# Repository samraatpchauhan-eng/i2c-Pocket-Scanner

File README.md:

# i2c Pocket Scanner
i2c Pocket scanner is a portable hardware debugging device, for scanning i2c modules' hexadecimal code and displaying it to the user. I designed it mainly for use if you use public makerspaces alot and don't have the space for a full hardware debugging kit, or need to verify if a part works on the go. 
## Features:
* **Miniature Layout:**  The i2c Pocket Scanner has a very small footprint, making it easy to carry it in your bag, or put it in your pocket!
* **OLED display:** There is a 0.91 inch oled screen to display the hexadecimal code received from the component being tested, and to verify the part actually works.
* **Simple Assembly:** Assembling the i2c Pocket Scanner is simple, and easy, as there is only the Seeed Xiao rp2040 and the OLED display to connect to the PCB.

---

## CAD Model
Due to the small size of the case, everything fits together nice and tight, without an risk of damage. There is also engravings on the case, describing what each header hole is so connecting external components becomes easy

### Case Assembly & Fitment
*A 3D CAD visualization highlighting how all the parts fit together seamlessly.*

---

## PCB Design
The underlying electronics were engineered in KiCad. The board features clean routing paths optimized for the RP2040 pin configurations and a direct connection layout to handle both the OLED display and the open header for connecting other components.

### Schematic Design
*The circuit schematic mapping the display routing, and header connections to the microcontroller.*

### PCB Layout Architecture
*The routed printed circuit board design detailing trace paths, footprints, and physical alignment.*

---

## How to Flash
1. Press and hold the physical **BOOT** button on the RP2040 controller board.
2. Connect the USB cable while holding the button, then release it.
3. A virtual drive named will mount to your operating system.
4. Drag and drop the `i2c-pocket-scanner.ino.uf2` binary file directly onto the root of the drive.
5. The device will automatically flash, reboot, and initialize as an operational device.

---

## AI Attribution Note
**Please Note that AI was utilized for some basic project planning and debugging of the firmware in VS.Code**

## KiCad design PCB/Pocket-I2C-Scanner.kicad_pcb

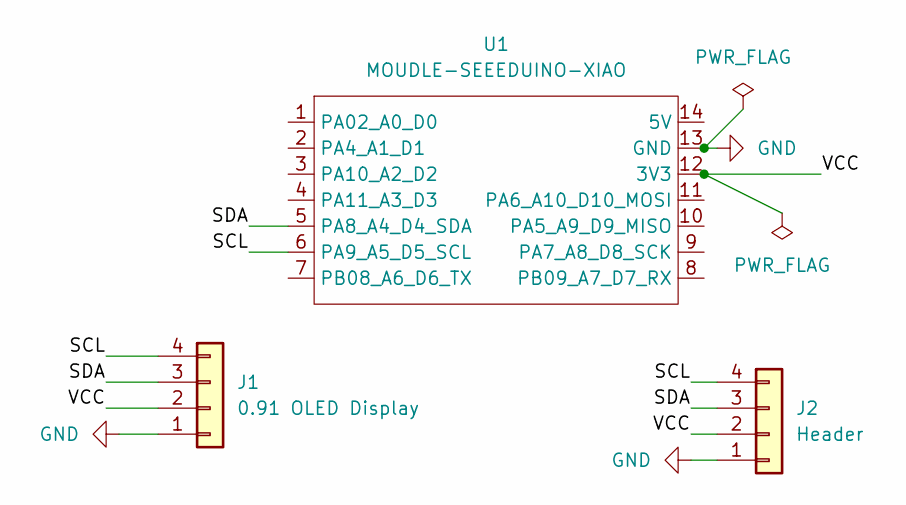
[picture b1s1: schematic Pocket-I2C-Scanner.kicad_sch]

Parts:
J1: 0.91 OLED Display; PinHeader_1x04_P2.54mm_Vertical
J2: Header; PinHeader_1x04_P2.54mm_Vertical
U1: MOUDLE-SEEEDUINO-XIAO; XIAO-Generic-Hybrid-14P-2.54-21X17.8MM

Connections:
/SCL: J1.4 (Pin_1), J2.4 (Pin_1), U1.6 (PA9_A5_D5_SCL)
/SDA: J1.3 (Pin_2), J2.3 (Pin_2), U1.5 (PA8_A4_D4_SDA)
/VCC: J1.2 (Pin_3), J2.2 (Pin_3), U1.12 (3V3)
GND: J1.1 (Pin_4), J2.1 (Pin_4), U1.13 (GND)

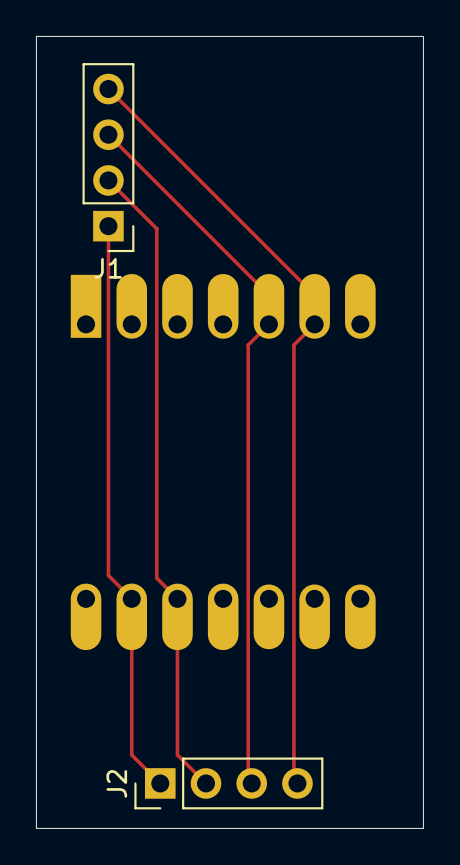
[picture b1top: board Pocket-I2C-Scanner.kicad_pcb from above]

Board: 2 copper layers, 21.5 x 44.0 mm, 3 parts (1 on the bottom side), 4 nets.
